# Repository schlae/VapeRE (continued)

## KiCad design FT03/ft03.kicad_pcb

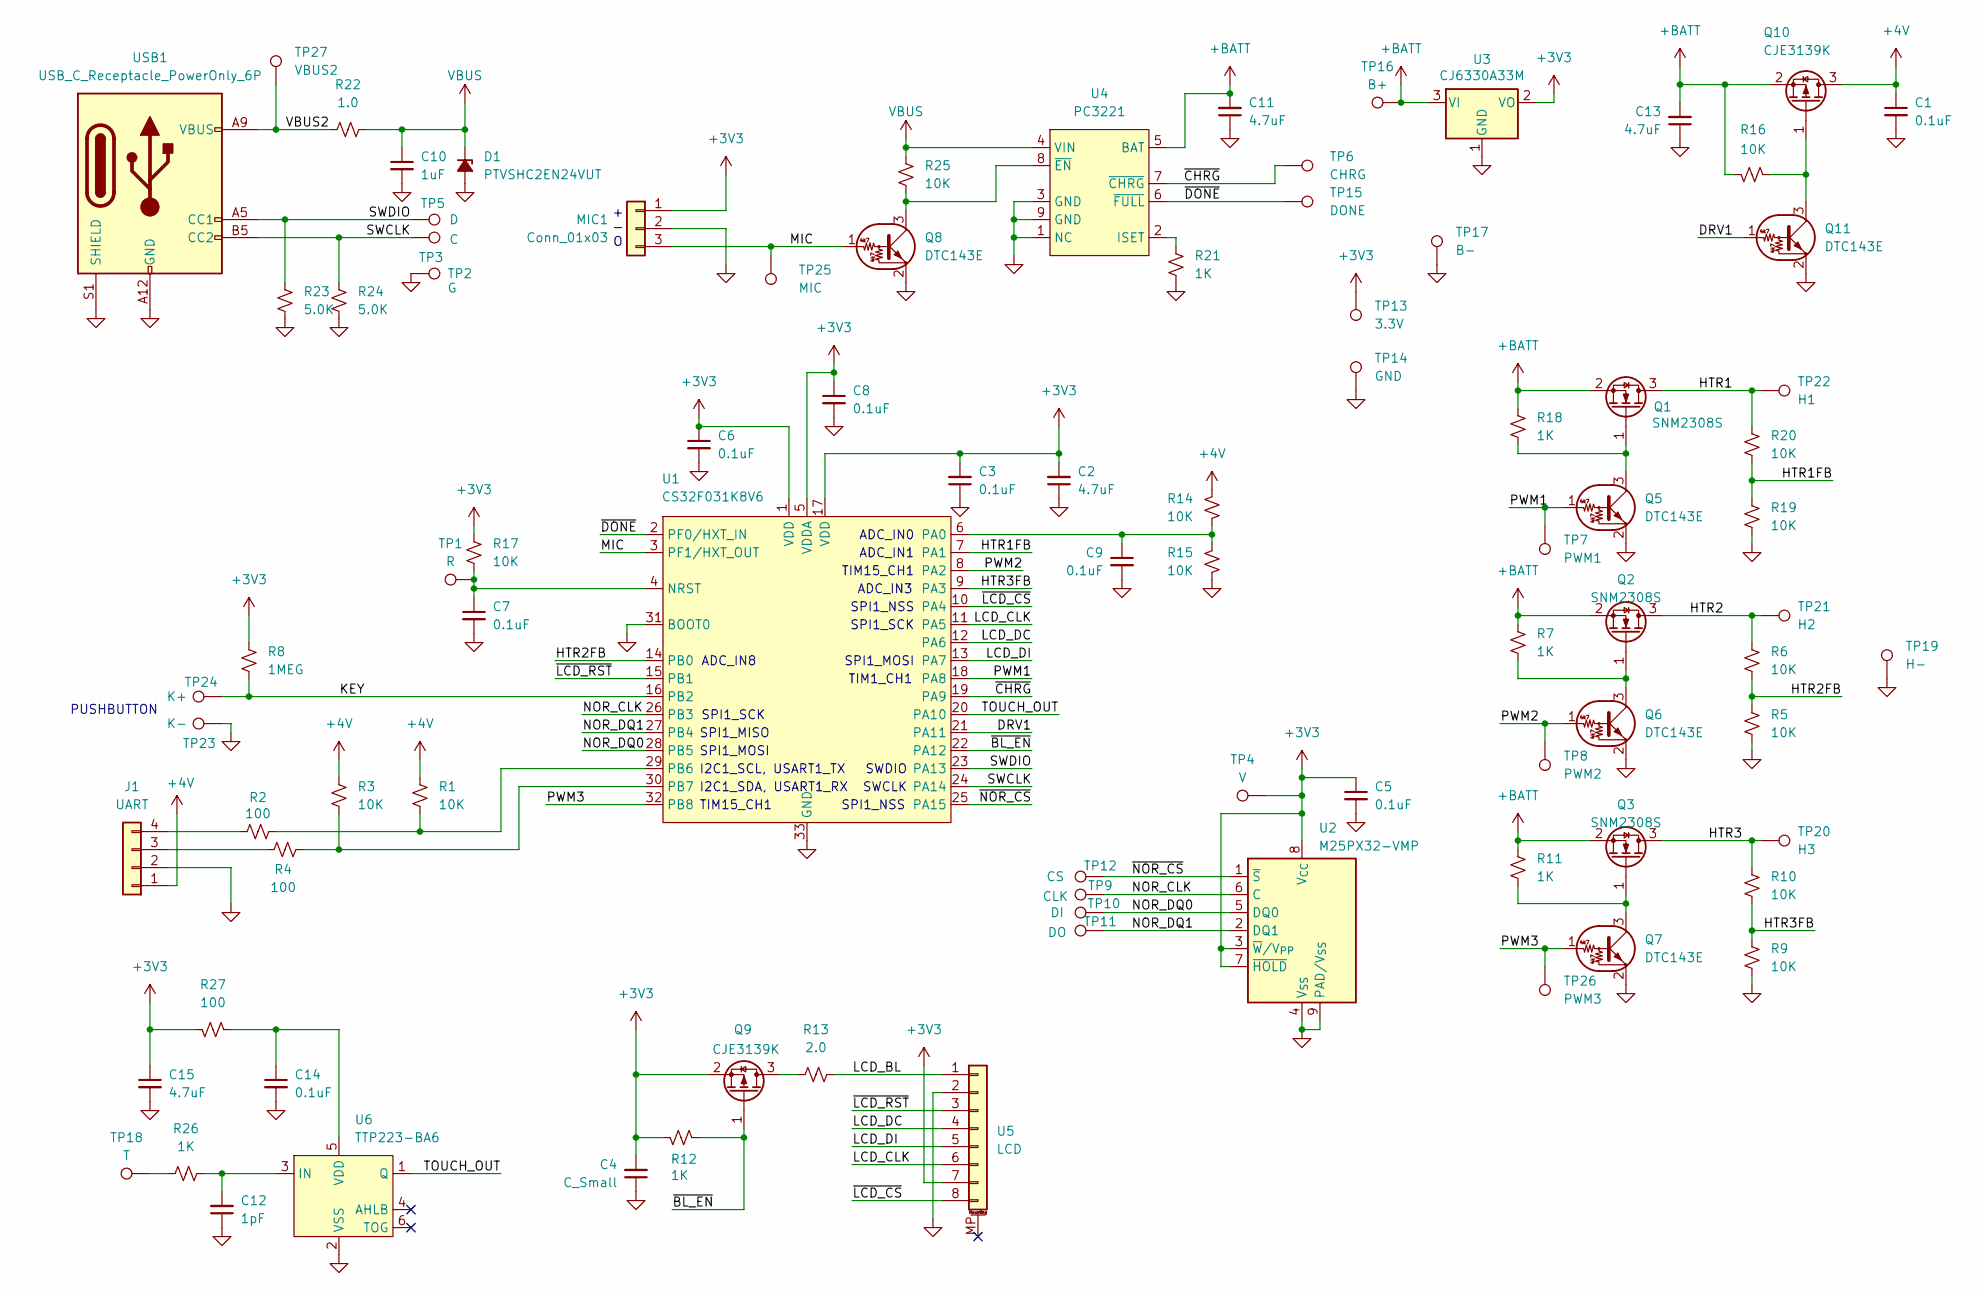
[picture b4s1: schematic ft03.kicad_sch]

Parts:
C1, C3, C5, C6, C7, C8, C9, C14: 0.1uF; C_0402_1005Metric
C2, C11, C13, C15: 4.7uF; C_0402_1005Metric
C4: C_Small; C_0402_1005Metric
C10: 1uF; C_0402_1005Metric
C12: 1pF; C_0402_1005Metric
D1: PTVSHC2EN24VUT; ST_QFN-2L_1.6x1.0mm
J1: UART; PinHeader_1x04_P2.00mm_Vertical
MIC1: Conn_01x03; MIC_3P
Q1, Q2, Q3: SNM2308S; SOT95P230X117-3
Q5, Q6, Q7, Q8, Q11: DTC143E; SOT-523
Q9, Q10: CJE3139K; SOT-523
R1, R3, R5, R6, R9, R10, R14, R15, R16, R17, R19, R20, R25: 10K; R_0402_1005Metric
R2, R4, R27: 100; R_0402_1005Metric
R7, R11, R12, R18, R21, R26: 1K; R_0402_1005Metric
R8: 1MEG; R_0402_1005Metric
R13: 2.0; R_0805_2012Metric
R22: 1.0; R_0805_2012Metric
R23, R24: 5.0K; R_0402_1005Metric
TP1: R; TestPoint_Pad_D1.0mm
TP2: G; TestPoint_Pad_D1.0mm
TP3: C; TestPoint_Pad_D1.0mm
TP4: V; TestPoint_Pad_D1.0mm
TP5: D; TestPoint_Pad_D1.0mm
TP6: CHRG; TestPoint_Pad_D1.0mm
TP7: PWM1; TestPoint_Pad_D1.0mm
TP8: PWM2; TestPoint_Pad_D1.0mm
TP9: CLK; TestPoint_Pad_D1.0mm
TP10: DI; TestPoint_Pad_D1.0mm
TP11: DO; TestPoint_Pad_D1.0mm
TP12: CS; TestPoint_Pad_D1.0mm
TP13: 3.3V; TestPoint_Pad_D1.0mm
TP14: GND; TestPoint_Pad_D1.0mm
TP15: DONE; TestPoint_Pad_D1.0mm
TP16: B+; TestPoint_Pad_D1.5mm
TP17: B-; TestPoint_Pad_D1.5mm
TP18: T; TestPoint_Pad_D1.5mm
TP19: H-; TestPoint_Pad_D1.5mm
TP20: H3; TestPoint_Pad_D1.5mm
TP21: H2; TestPoint_Pad_D1.5mm
TP22: H1; TestPoint_Pad_D1.5mm
TP23: K-; TestPoint_Pad_D1.5mm
TP24: K+; TestPoint_Pad_D1.5mm
TP25: MIC; TestPoint_Pad_D1.0mm
TP26: PWM3; TestPoint_Pad_D1.0mm
TP27: VBUS2; TestPoint_Pad_D1.5mm
U1: CS32F031K8V6; QFN-32-1EP_4x4mm_P0.4mm_EP2.9x2.9mm
U2: M25PX32-VMP; Winbond_USON-8-1EP_3x2mm_P0.5mm_EP0.2x1.6mm
U3: CJ6330A33M; SOT95P230X117-3
U4: PC3221; HSOP-8-1EP_3.9x4.9mm_P1.27mm_EP2.41x3.1mm
U5: LCD; UNK_FPC_1x08-1MP_P0.5mm_Horizontal
U6: TTP223-BA6; SOT95P305X110-6
USB1: USB_C_Receptacle_PowerOnly_6P; USB_C_Receptacle_HRO_TYPE-C-31-M-17

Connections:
+3V3: C2.2, C3.2, C4.2, C5.1, C6.1, C8.1, C15.1, MIC1.1, Q9.2 (S), R8.2, R12.1, R17.1, R27.2, TP4.1, TP13.1, U1.1 (VDD), U1.5 (VDDA), U1.17 (VDD), U2.3 (~W/V_{PP}), U2.7 (~HOLD), U2.8 (V_{CC}), U3.2 (VO), U5.7
+4V: C1.1, J1.1, Q10.3 (D), R1.1, R3.1, R14.2
+BATT: C11.2, C13.2, Q1.2 (S), Q2.2 (S), Q3.2 (S), Q10.2 (S), R7.1, R11.2, R16.2, R18.2, TP16.1, U3.3 (VI), U4.5 (BAT)
/DRV1: Q11.1 (B), U1.21 (PA11)
/HTR1: Q1.3 (D), R20.1, TP22.1
/HTR1FB: R19.1, R20.2, U1.7 (PA1)
/HTR2: Q2.3 (D), R6.1, TP21.1
/HTR2FB: R5.2, R6.2, U1.14 (PB0)
/HTR3: Q3.3 (D), R10.2, TP20.1
/HTR3FB: R9.1, R10.1, U1.9 (PA3)
/KEY: R8.1, TP24.1, U1.16 (PB2)
/LCD_BL: R13.2, U5.1
/LCD_CLK: U1.11 (PA5), U5.6
/LCD_DC: U1.12 (PA6), U5.4
/LCD_DI: U1.13 (PA7), U5.5
/MIC: MIC1.3, Q8.1 (B), TP25.1, U1.3 (PF1/HXT_OUT)
/NOR_CLK: TP9.1, U1.26 (PB3), U2.6 (C)
/NOR_DQ0: TP10.1, U1.28 (PB5), U2.5 (DQ0)
/NOR_DQ1: TP11.1, U1.27 (PB4), U2.2 (DQ1)
/PWM1: Q5.1 (B), TP7.1, U1.18 (PA8)
/PWM2: Q6.1 (B), TP8.1, U1.8 (PA2)
/PWM3: Q7.1 (B), TP26.1, U1.32 (PB8)
/SWCLK: R24.1, TP3.1, U1.24 (PA14), USB1.B5 (CC2)
/SWDIO: R23.1, TP5.1, U1.23 (PA13), USB1.A5 (CC1)
/TOUCH_OUT: U1.20 (PA10), U6.1 (Q)
/VBUS2: R22.2, TP27.1, USB1.A9 (VBUS), USB1.B9 (VBUS)
/~BL_EN: Q9.1 (G), R12.2, U1.22 (PA12)
/~CHRG: TP6.1, U1.19 (PA9), U4.7 (~CHRG)
/~DONE: TP15.1, U1.2 (PF0/HXT_IN), U4.6 (~FULL)
/~LCD_CS: U1.10 (PA4), U5.8
/~LCD_RST: U1.15 (PB1), U5.3
/~NOR_CS: TP12.1, U1.25 (PA15), U2.1 (~S)
GND: C1.2, C2.1, C3.1, C4.1, C5.2, C6.2, C7.2, C8.2, C9.2, C10.2, C11.1, C12.1, C13.1, C14.2, C15.2, D1.2 (A), J1.2, MIC1.2, Q5.2 (E), Q6.2 (E), Q7.2 (E), Q8.2 (E), Q11.2 (E), R5.1, R9.2, R15.1, R19.2, R21.2, R23.2, R24.2, TP2.1, TP14.1, TP17.1, TP19.1, TP23.1, U1.31 (BOOT0), U1.33 (GND), U2.4 (V_{SS}), U2.9 (PAD/V_{SS}), U3.1 (GND), U4.1 (NC), U4.3 (GND), U4.9 (GND), U5.2, U6.2 (VSS), USB1.A12 (GND), USB1.B12 (GND), USB1.S1 (SHIELD)
unnamed: J1.3, R4.1
unnamed: J1.4, R2.1
unnamed: Q1.1 (G), Q5.3 (C), R18.1
unnamed: Q2.1 (G), Q6.3 (C), R7.2
unnamed: Q3.1 (G), Q7.3 (C), R11.1
unnamed: Q8.3 (C), R25.1, U4.8 (~EN)
unnamed: Q9.3 (D), R13.1
unnamed: Q10.1 (G), Q11.3 (C), R16.1
unnamed: R26.1, TP18.1
unnamed: C7.1, R17.2, TP1.1, U1.4 (NRST)
unnamed: C9.1, R14.1, R15.2, U1.6 (PA0)
unnamed: R1.2, R2.2, U1.29 (PB6)
unnamed: R3.2, R4.2, U1.30 (PB7)
unnamed: R21.1, U4.2 (ISET)
unnamed: C12.2, R26.2, U6.3 (IN)
unnamed: C14.1, R27.1, U6.5 (VDD)
VBUS: C10.1, D1.1 (K), R22.1, R25.2, U4.4 (VIN)

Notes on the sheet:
SPI1_NSS
I2C1_SCL, USART1_TX
SPI1_SCK
SWDIO
ADC_IN1
SPI1_MOSI
I2C1_SDA, USART1_RX
SPI1_MISO
TIM1_CH1
TIM15_CH1
PUSHBUTTON
SWCLK
ADC_IN0
ADC_IN8
ADC_IN3
+ - O

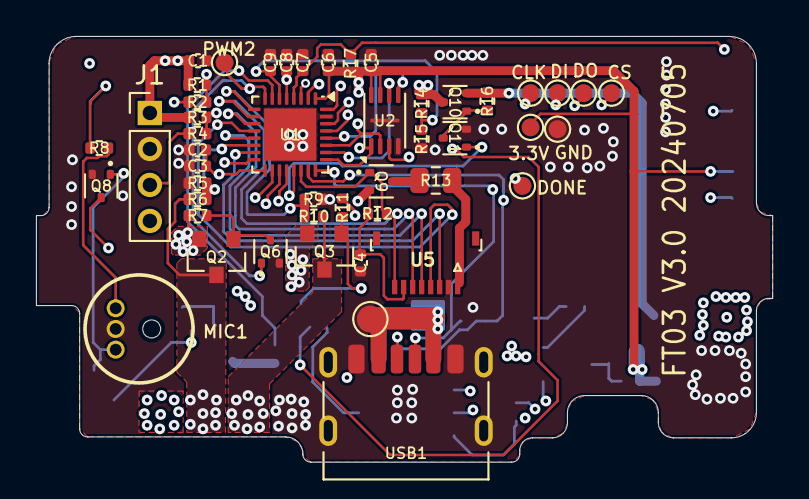
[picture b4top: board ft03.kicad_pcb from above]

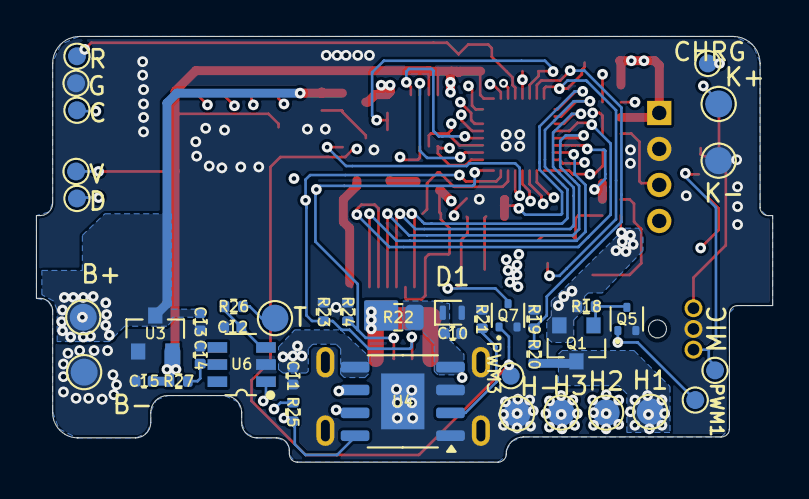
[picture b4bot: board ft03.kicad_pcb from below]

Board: 4 copper layers, 40.9 x 23.7 mm, 89 parts (41 on the bottom side), 50 nets.

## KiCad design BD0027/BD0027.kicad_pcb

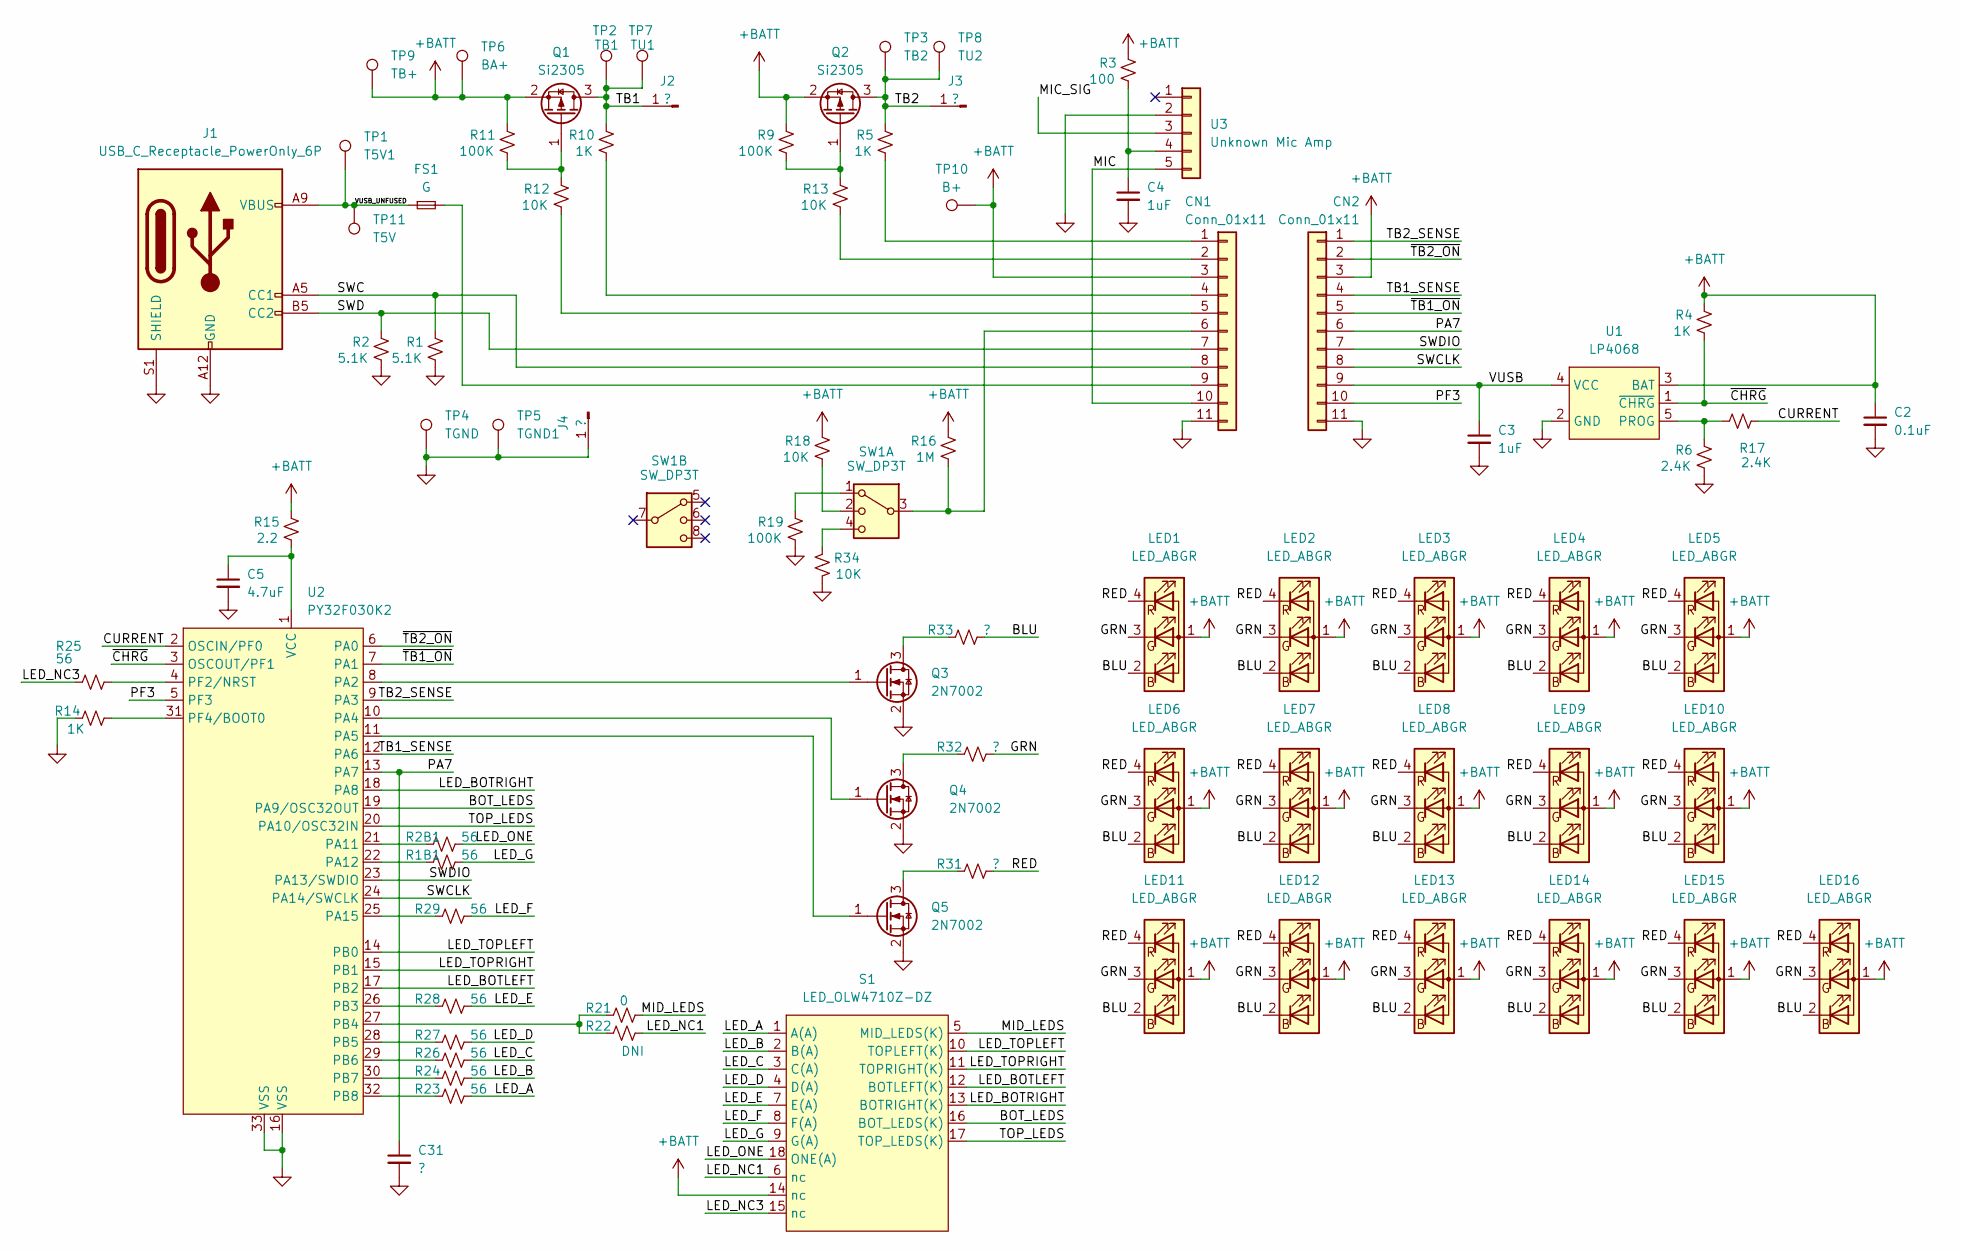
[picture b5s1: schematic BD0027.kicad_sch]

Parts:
C2: 0.1uF; C_0402_1005Metric
C3, C4: 1uF; C_0402_1005Metric
C5: 4.7uF; C_0402_1005Metric
C31: ?; C_0402_1005Metric
CN1, CN2: Conn_01x11; PinHeader_1x11_P1.00mm_Vertical
FS1: G; Fuse_0603_1608Metric
J1: USB_C_Receptacle_PowerOnly_6P; USB_C_Receptacle_TYPE-C-VERT
J2, J3, J4: ?; Pin_D1.2mm_L10.2mm_W2.9mm_FlatFork
LED1, LED2, LED3, LED4, LED5, LED6, LED7, LED8, LED9, LED10, LED11, LED12, LED13, LED14, LED15, LED16: LED_ABGR; LED_SK6812_EC15_1.5x1.5mm
Q1, Q2: Si2305; SOT95P230X117-3
Q3, Q4, Q5: 2N7002; SOT-523
R1, R2: 5.1K; R_0402_1005Metric
R1B1, R2B1, R23, R24, R25, R26, R27, R28, R29: 56; R_0402_1005Metric
R3: 100; R_0402_1005Metric
R4, R5, R10, R14: 1K; R_0402_1005Metric
R6, R17: 2.4K; R_0402_1005Metric
R9, R11, R19: 100K; R_0402_1005Metric
R12, R13, R18, R34: 10K; R_0402_1005Metric
R15: 2.2; R_0402_1005Metric
R16: 1M; R_0402_1005Metric
R21: 0; R_0402_1005Metric
R22: DNI; R_0402_1005Metric
R31, R32, R33: ?; R_0805_2012Metric
S1: LED_OLW4710Z-DZ; OLW4710Z-DZ
SW1: SW_DP3T; SW_DP3T_SMD
TP1: T5V1; TestPoint_Pad_D1.5mm
TP2: TB1; TestPoint_Pad_D1.5mm
TP3: TB2; TestPoint_Pad_D1.5mm
TP4: TGND; TestPoint_Pad_D1.5mm
TP5: TGND1; TestPoint_Pad_D1.5mm
TP6: BA+; TestPoint_Pad_D1.5mm
TP7: TU1; TestPoint_Pad_D1.5mm
TP8: TU2; TestPoint_Pad_D1.5mm
TP9: TB+; TestPoint_Pad_D1.5mm
TP10: B+; TestPoint_Pad_D1.5mm
TP11: T5V; TestPoint_Pad_D1.5mm
U1: LP4068; TSOP-5_1.65x3.05mm_P0.95mm
U2: PY32F030K2; QFN-32-1EP_5x5mm_P0.5mm_EP3.45x3.45mm
U3: Unknown Mic Amp; SOT-23-5

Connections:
+BATT: C2.1, CN1.3, CN2.3, LED1.1 (A), LED2.1 (A), LED3.1 (A), LED4.1 (A), LED5.1 (A), LED6.1 (A), LED7.1 (A), LED8.1 (A), LED9.1 (A), LED10.1 (A), LED11.1 (A), LED12.1 (A), LED13.1 (A), LED14.1 (A), LED15.1 (A), LED16.1 (A), Q1.2 (S), Q2.2 (S), R3.2, R4.2, R9.2, R11.2, R15.2, R16.2, R18.2, S1.14 (nc), TP6.1, TP9.1, TP10.1, U1.3 (BAT)
/BLU: LED1.2 (BK), LED2.2 (BK), LED3.2 (BK), LED4.2 (BK), LED5.2 (BK), LED6.2 (BK), LED7.2 (BK), LED8.2 (BK), LED9.2 (BK), LED10.2 (BK), LED11.2 (BK), LED12.2 (BK), LED13.2 (BK), LED14.2 (BK), LED15.2 (BK), LED16.2 (BK), R33.1
/BOT_LEDS: S1.16 (BOT_LEDS(K)), U2.19 (PA9/OSC32OUT)
/CURRENT: R17.1, U2.2 (OSCIN/PF0)
/GRN: LED1.3 (GK), LED2.3 (GK), LED3.3 (GK), LED4.3 (GK), LED5.3 (GK), LED6.3 (GK), LED7.3 (GK), LED8.3 (GK), LED9.3 (GK), LED10.3 (GK), LED11.3 (GK), LED12.3 (GK), LED13.3 (GK), LED14.3 (GK), LED15.3 (GK), LED16.3 (GK), R32.1
/LED_A: R23.1, S1.1 (A(A))
/LED_B: R24.1, S1.2 (B(A))
/LED_BOTLEFT: S1.12 (BOTLEFT(K)), U2.17 (PB2)
/LED_BOTRIGHT: S1.13 (BOTRIGHT(K)), U2.18 (PA8)
/LED_C: R26.1, S1.3 (C(A))
/LED_D: R27.1, S1.4 (D(A))
/LED_E: R28.1, S1.7 (E(A))
/LED_F: R29.1, S1.8 (F(A))
/LED_G: R1B1.1, S1.9 (G(A))
/LED_NC1: R22.1, S1.6 (nc)
/LED_NC3: R25.1, S1.15 (nc)
/LED_ONE: R2B1.1, S1.18 (ONE(A))
/LED_TOPLEFT: S1.10 (TOPLEFT(K)), U2.14 (PB0)
/LED_TOPRIGHT: S1.11 (TOPRIGHT(K)), U2.15 (PB1)
/MIC: CN1.10, U3.5
/MIC_SIG: U3.3
/MID_LEDS: R21.1, S1.5 (MID_LEDS(K))
/PA7: C31.1, CN2.6, U2.13 (PA7)
/PF3: CN2.10, U2.5 (PF3)
/RED: LED1.4 (RK), LED2.4 (RK), LED3.4 (RK), LED4.4 (RK), LED5.4 (RK), LED6.4 (RK), LED7.4 (RK), LED8.4 (RK), LED9.4 (RK), LED10.4 (RK), LED11.4 (RK), LED12.4 (RK), LED13.4 (RK), LED14.4 (RK), LED15.4 (RK), LED16.4 (RK), R31.1
/SWC: CN1.8, J1.A5 (CC1), R1.2
/SWCLK: CN2.8, U2.24 (PA14/SWCLK)
/SWD: CN1.7, J1.B5 (CC2), R2.2
/SWDIO: CN2.7, U2.23 (PA13/SWDIO)
/TB1: J2.1, Q1.3 (D), R10.2, TP2.1, TP7.1
/TB1_SENSE: CN2.4, U2.12 (PA6)
/TB2: J3.1, Q2.3 (D), R5.2, TP3.1, TP8.1
/TB2_SENSE: CN2.1, U2.9 (PA3)
/TOP_LEDS: S1.17 (TOP_LEDS(K)), U2.20 (PA10/OSC32IN)
/VUSB: C3.1, CN2.9, U1.4 (VCC)
/VUSB_UNFUSED: FS1.1, J1.A9 (VBUS), J1.B9 (VBUS), TP1.1, TP11.1
/~CHRG: R4.1, U1.1 (~CHRG), U2.3 (OSCOUT/PF1)
/~TB1_ON: CN2.5, U2.7 (PA1)
/~TB2_ON: CN2.2, U2.6 (PA0)
GND: C2.2, C3.2, C4.2, C5.2, C31.2, CN1.11, CN2.11, J1.A12 (GND), J1.B12 (GND), J1.S1 (SHIELD), J4.1, Q3.2 (S), Q4.2 (S), Q5.2 (S), R1.1, R2.1, R6.1, R14.2, R19.1, R34.1, TP4.1, TP5.1, U1.2 (GND), U2.16 (VSS), U2.33 (VSS), U3.2
unnamed: CN1.1, R5.1
unnamed: CN1.2, R13.1
unnamed: CN1.4, R10.1
unnamed: CN1.5, R12.1
unnamed: CN1.6, R16.1, SW1.3
unnamed: CN1.9, FS1.2
unnamed: Q1.1 (G), R11.1, R12.2
unnamed: Q2.1 (G), R9.1, R13.2
unnamed: Q3.3 (D), R33.2
unnamed: Q3.1 (G), U2.8 (PA2)
unnamed: Q4.3 (D), R32.2
unnamed: Q4.1 (G), U2.10 (PA4)
unnamed: Q5.3 (D), R31.2
unnamed: Q5.1 (G), U2.11 (PA5)
unnamed: R18.1, SW1.2
unnamed: R19.2, SW1.1
unnamed: R34.2, SW1.4
unnamed: R6.2, R17.2, U1.5 (PROG)
unnamed: R2B1.2, U2.21 (PA11)
unnamed: R1B1.2, U2.22 (PA12)
unnamed: R29.2, U2.25 (PA15)
unnamed: R28.2, U2.26 (PB3)
unnamed: R21.2, R22.2, U2.27 (PB4)
unnamed: R27.2, U2.28 (PB5)
unnamed: R26.2, U2.29 (PB6)
unnamed: R24.2, U2.30 (PB7)
unnamed: R23.2, U2.32 (PB8)
unnamed: R25.2, U2.4 (PF2/NRST)
unnamed: R14.1, U2.31 (PF4/BOOT0)
unnamed: C5.1, R15.1, U2.1 (VCC)
unnamed: C4.1, R3.1, U3.4

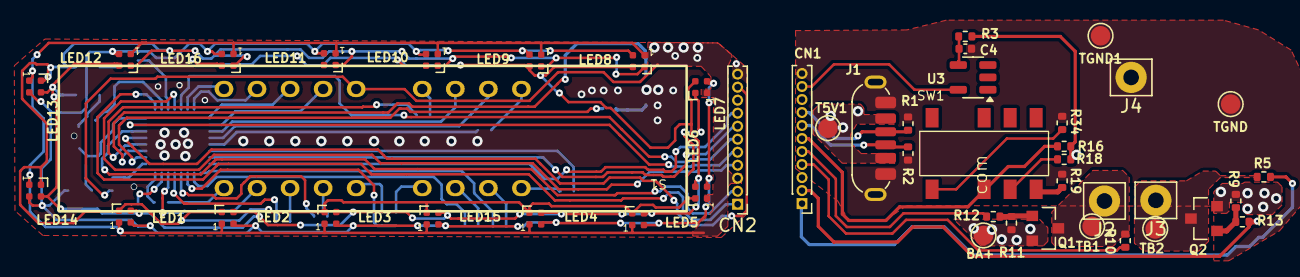
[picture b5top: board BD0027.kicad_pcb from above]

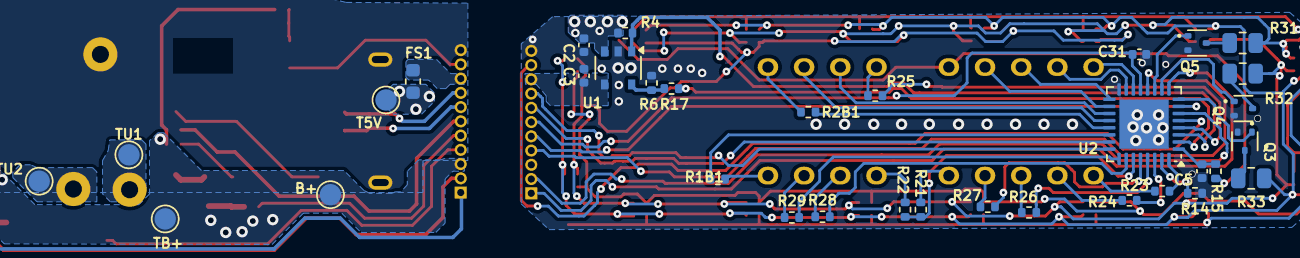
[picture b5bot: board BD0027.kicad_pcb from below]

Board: 2 copper layers, 81 parts (34 on the bottom side), 70 nets.

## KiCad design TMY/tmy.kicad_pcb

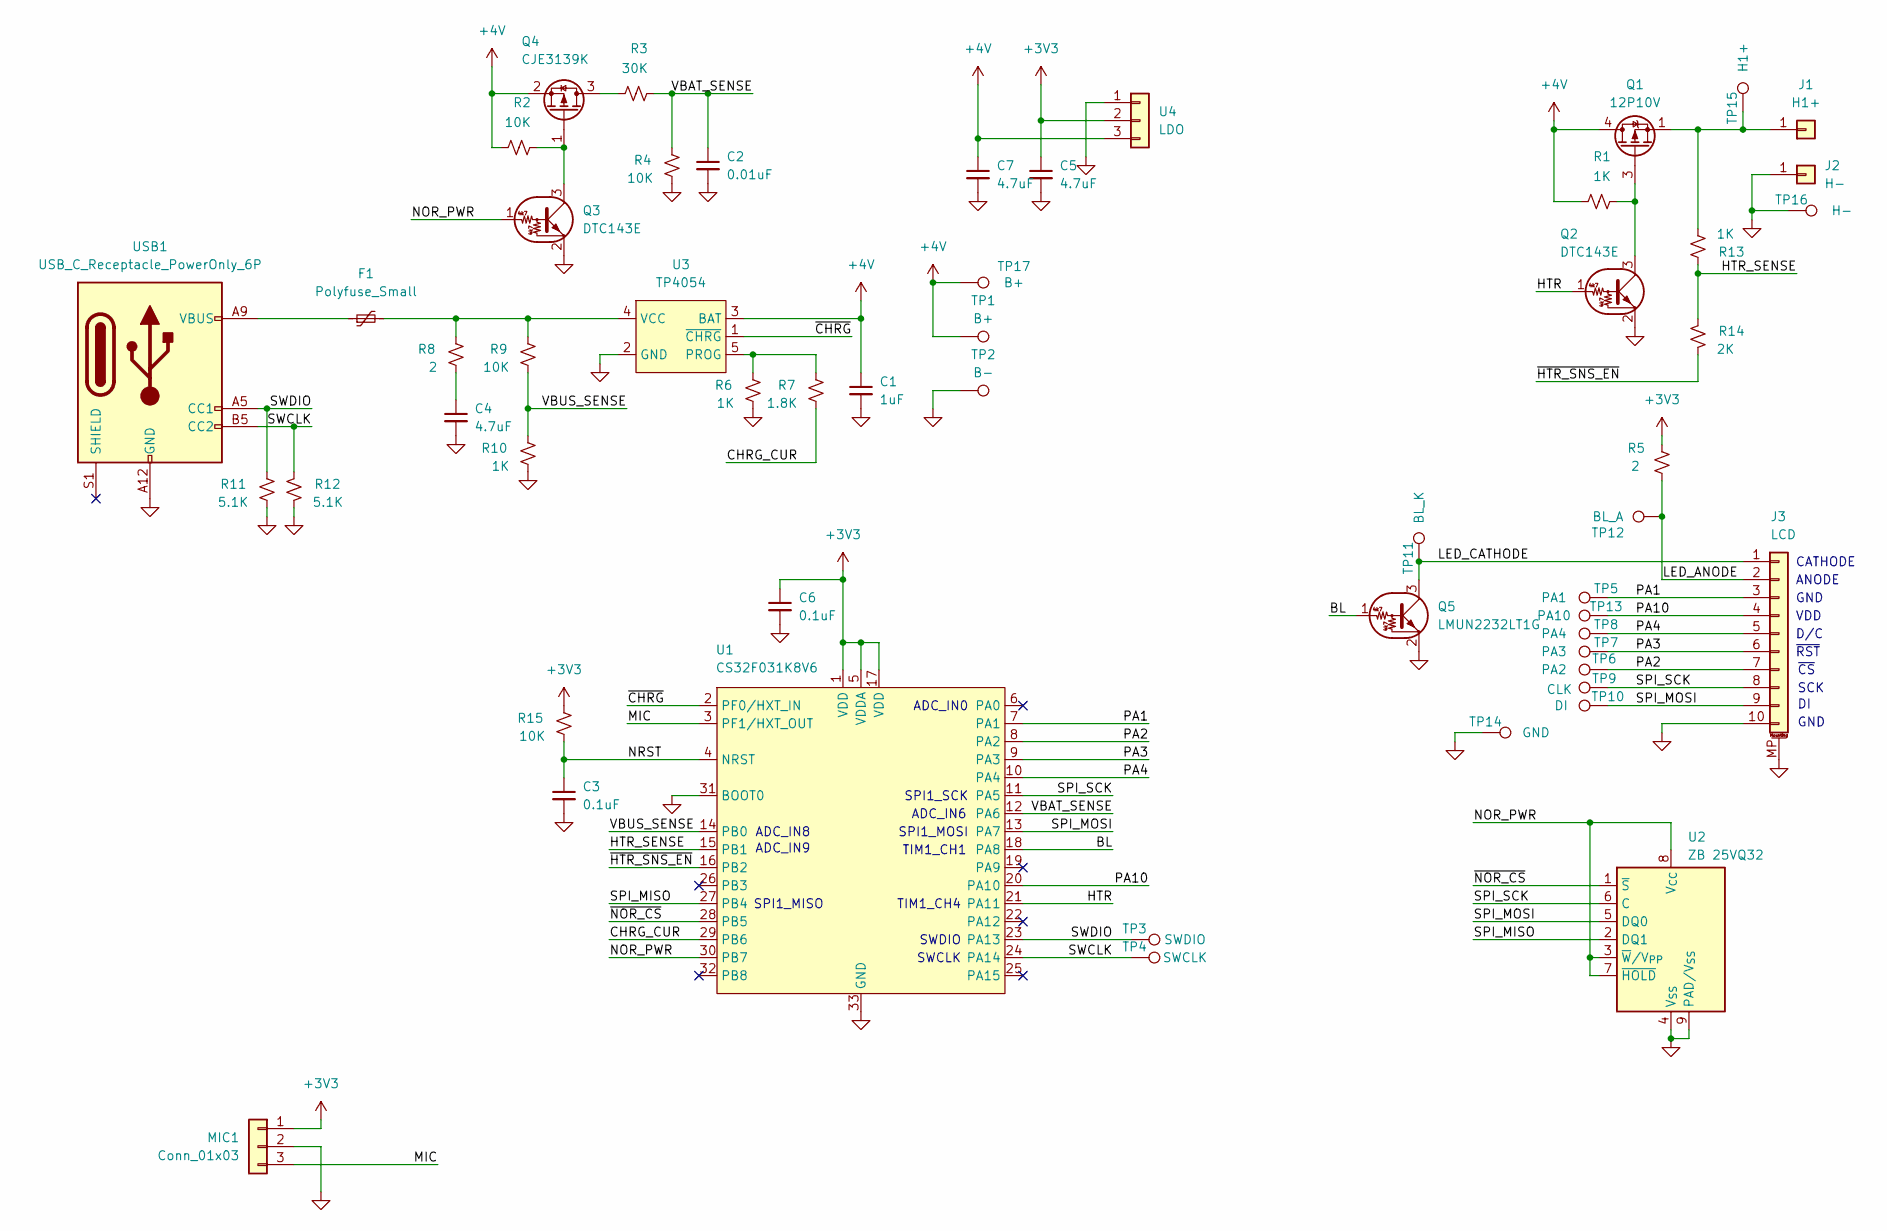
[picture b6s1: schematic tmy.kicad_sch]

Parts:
C1: 1uF; C_0402_1005Metric
C2: 0.01uF; C_0402_1005Metric
C3, C6: 0.1uF; C_0402_1005Metric
C4, C5, C7: 4.7uF; C_0402_1005Metric
F1: Polyfuse_Small; Fuse_0603_1608Metric
J1: H1+; TestPoint_THTPad_D1.5mm_Drill0.7mm
J2: H-; TestPoint_THTPad_D1.5mm_Drill0.7mm
J3: LCD; UNK_FPC_1x10-1MP_P0.5mm_Horizontal
MIC1: Conn_01x03; MIC_3P_Alt
Q1: 12P10V; Texas_DQK
Q2, Q3: DTC143E; SOT-523
Q4: CJE3139K; SOT-523
Q5: LMUN2232LT1G; SC-59
R1, R6, R10, R13: 1K; R_0402_1005Metric
R2, R4, R9, R15: 10K; R_0402_1005Metric
R3: 30K; R_0402_1005Metric
R5: 2; R_0603_1608Metric
R7: 1.8K; R_0402_1005Metric
R8: 2; R_0402_1005Metric
R11, R12: 5.1K; R_0402_1005Metric
R14: 2K; R_0402_1005Metric
TP1, TP17: B+; TestPoint_Pad_D1.5mm
TP2: B-; TestPoint_Pad_D1.5mm
TP3: SWDIO; TestPoint_Pad_D1.0mm
TP4: SWCLK; TestPoint_Pad_D1.0mm
TP5: PA1; TestPoint_Pad_D1.0mm
TP6: PA2; TestPoint_Pad_D1.0mm
TP7: PA3; TestPoint_Pad_D1.0mm
TP8: PA4; TestPoint_Pad_D1.0mm
TP9: CLK; TestPoint_Pad_D1.0mm
TP10: DI; TestPoint_Pad_D1.0mm
TP11: BL_K; TestPoint_Pad_D1.0mm
TP12: BL_A; TestPoint_Pad_D1.0mm
TP13: PA10; TestPoint_Pad_D1.0mm
TP14: GND; TestPoint_Pad_D1.0mm
TP15: H1+; TestPoint_Pad_D1.0mm
TP16: H-; TestPoint_Pad_D1.0mm
U1: CS32F031K8V6; QFN-32-1EP_4x4mm_P0.4mm_EP2.9x2.9mm
U2: ZB 25VQ32; Winbond_USON-8-1EP_3x2mm_P0.5mm_EP0.2x1.6mm
U3: TP4054; TSOP-5_1.65x3.05mm_P0.95mm
U4: LDO; SOT95P230X117-3
USB1: USB_C_Receptacle_PowerOnly_6P; USB_C_Receptacle_TYPE-C-VERT

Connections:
+3V3: C5.1, C6.1, MIC1.1, R5.2, R15.2, U1.1 (VDD), U1.5 (VDDA), U1.17 (VDD), U4.2
+4V: C1.1, C7.1, Q1.4 (D), Q1.7 (D), Q4.2 (S), R1.1, R2.1, TP1.1, TP17.1, U3.3 (BAT), U4.3
/BL: Q5.1 (B), U1.18 (PA8)
/CHRG_CUR: R7.1, U1.29 (PB6)
/HTR: Q2.1 (B), U1.21 (PA11)
/HTR_SENSE: R13.2, R14.2, U1.15 (PB1)
/LED_ANODE: J3.2, R5.1, TP12.1
/LED_CATHODE: J3.1, Q5.3 (C), TP11.1
/MIC: MIC1.3, U1.3 (PF1/HXT_OUT)
/NOR_PWR: Q3.1 (B), U1.30 (PB7), U2.3 (~W/V_{PP}), U2.7 (~HOLD), U2.8 (V_{CC})
/NRST: C3.1, R15.1, U1.4 (NRST)
/PA1: J3.3, TP5.1, U1.7 (PA1)
/PA2: J3.7, TP6.1, U1.8 (PA2)
/PA3: J3.6, TP7.1, U1.9 (PA3)
/PA4: J3.5, TP8.1, U1.10 (PA4)
/PA10: J3.4, TP13.1, U1.20 (PA10)
/SPI_MISO: U1.27 (PB4), U2.2 (DQ1)
/SPI_MOSI: J3.9, TP10.1, U1.13 (PA7), U2.5 (DQ0)
/SPI_SCK: J3.8, TP9.1, U1.11 (PA5), U2.6 (C)
/SWCLK: R12.2, TP4.1, U1.24 (PA14), USB1.B5 (CC2)
/SWDIO: R11.2, TP3.1, U1.23 (PA13), USB1.A5 (CC1)
/VBAT_SENSE: C2.1, R3.2, R4.2, U1.12 (PA6)
/VBUS_SENSE: R9.1, R10.2, U1.14 (PB0)
/~CHRG: U1.2 (PF0/HXT_IN), U3.1 (~CHRG)
/~HTR_SNS_EN: R14.1, U1.16 (PB2)
/~NOR_CS: U1.28 (PB5), U2.1 (~S)
GND: C1.2, C2.2, C3.2, C4.2, C5.2, C6.2, C7.2, J2.1, J3.10, J3.MP (MountPin), MIC1.2, Q2.2 (E), Q3.2 (E), Q5.2 (E), R4.1, R6.1, R10.1, R11.1, R12.1, TP2.1, TP14.1, TP16.1, U1.31 (BOOT0), U1.33 (GND), U2.4 (V_{SS}), U2.9 (PAD/V_{SS}), U3.2 (GND), U4.1, USB1.A12 (GND), USB1.B12 (GND)
unnamed: C4.1, R8.1
unnamed: F1.1, USB1.A9 (VBUS), USB1.B9 (VBUS)
unnamed: J1.1, Q1.1 (S), Q1.2 (S), Q1.5 (S), Q1.6 (S), Q1.8 (S), R13.1, TP15.1
unnamed: Q1.3 (G), Q2.3 (C), R1.2
unnamed: Q3.3 (C), Q4.1 (G), R2.2
unnamed: Q4.3 (D), R3.1
unnamed: R6.2, R7.2, U3.5 (PROG)
unnamed: F1.2, R8.2, R9.2, U3.4 (VCC)

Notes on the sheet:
SPI1_SCK
~{CS}
~{RST}
TIM1_CH4
ADC_IN6
SCK
SWCLK
ADC_IN8
ADC_IN9
GND
TIM1_CH1
ADC_IN0
SWDIO
SPI1_MISO
ANODE
SPI1_MOSI
CATHODE
D/C
VDD

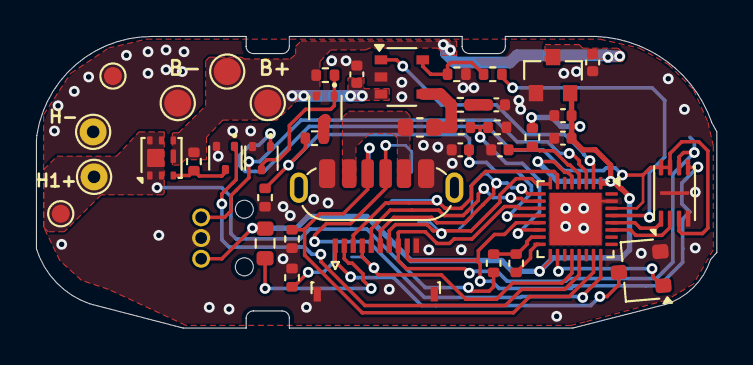
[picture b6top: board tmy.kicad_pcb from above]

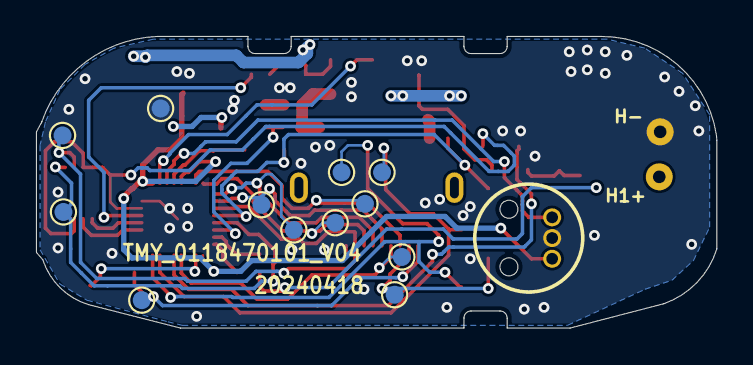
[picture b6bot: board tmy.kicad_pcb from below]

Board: 2 copper layers, 37.8 x 16.2 mm, 54 parts (13 on the bottom side), 35 nets.

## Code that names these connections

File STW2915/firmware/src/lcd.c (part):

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#include "nor.h"

#define LCD_PWR GPIO_PIN_8
#define LCD_DC GPIO_PIN_15
#define LCD_CS GPIO_PIN_7
#define LCD_RST GPIO_PIN_6
#define LCD_BACKLIGHT GPIO_PIN_8

#define CMD_NOP         0x00
#define CMD_PRIVATE     0xFD
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    HAL_GPIO_WritePin(GPIOA, LCD_PWR, GPIO_PIN_RESET);

    // Turn on LCD backlight
    HAL_GPIO_Init(GPIOB, &(GPIO_InitTypeDef){.Mode = GPIO_MODE_OUTPUT_PP, .Pin = LCD_BACKLIGHT});
    HAL_GPIO_WritePin(GPIOB, LCD_BACKLIGHT, GPIO_PIN_RESET);
    // Configure SPI for LCD
    // DI = PB5
    // CLK = PB3
    // RST = PB6
    // CS = PB7
    // C#/D = PA15
    HAL_GPIO_Init(GPIOB, &(GPIO_InitTypeDef){.Mode = GPIO_MODE_AF_PP, .Alternate = GPIO_AF0_SPI1, .Pin = GPIO_PIN_5});
    HAL_GPIO_Init(GPIOB, &(GPIO_InitTypeDef){.Mode = GPIO_MODE_AF_PP, .Alternate = GPIO_AF0_SPI1, .Pin = GPIO_PIN_3});

    HAL_GPIO_Init(GPIOB, &(GPIO_InitTypeDef){.Mode = GPIO_MODE_OUTPUT_PP, .Pin = LCD_RST});
    HAL_GPIO_WritePin(GPIOB, LCD_RST, GPIO_PIN_RESET);
    HAL_GPIO_Init(GPIOB, &(GPIO_InitTypeDef){.Mode = GPIO_MODE_OUTPUT_PP, .Pin = LCD_CS});
    HAL_GPIO_WritePin(GPIOB, LCD_CS, GPIO_PIN_RESET);
    HAL_GPIO_Init(GPIOA, &(GPIO_InitTypeDef){.Mode = GPIO_MODE_OUTPUT_PP, .Pin = LCD_DC});
    HAL_GPIO_WritePin(GPIOB, LCD_DC, GPIO_PIN_RESET);
}


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
static inline void mode_cmd()
{
    HAL_GPIO_WritePin(GPIOA, LCD_DC, GPIO_PIN_RESET);
}


static inline void mode_data()
{
    HAL_GPIO_WritePin(GPIOA, LCD_DC, GPIO_PIN_SET);
}


static inline void cs_low()
{
    HAL_GPIO_WritePin(GPIOB, LCD_CS, GPIO_PIN_RESET);
}


static inline void cs_high()
{
    HAL_GPIO_WritePin(GPIOB, LCD_CS, GPIO_PIN_SET);
}


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{
    _x_offset = 18;
    _y_offset = 82;
    HAL_GPIO_WritePin(GPIOB, LCD_CS, GPIO_PIN_SET);
    HAL_Delay(24);
    HAL_GPIO_WritePin(GPIOB, LCD_RST, GPIO_PIN_SET);
    HAL_Delay(6);
    HAL_GPIO_WritePin(GPIOB, LCD_RST, GPIO_PIN_RESET);
    HAL_Delay(50);
    HAL_GPIO_WritePin(GPIOB, LCD_RST, GPIO_PIN_SET);
    HAL_Delay(100); // Needed delay to allow LCD to init properly.

    // Configure registers
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    __HAL_RCC_DMA_CLK_DISABLE();
 
    // Turn off LCD backlight
    HAL_GPIO_WritePin(GPIOB, LCD_BACKLIGHT, GPIO_PIN_SET);

    // Float LCD controller pins
    HAL_GPIO_Init(GPIOB, &(GPIO_InitTypeDef){.Mode = GPIO_MODE_ANALOG, .Pin = GPIO_PIN_5});
    HAL_GPIO_Init(GPIOB, &(GPIO_InitTypeDef){.Mode = GPIO_MODE_ANALOG, .Pin = GPIO_PIN_3});
    HAL_GPIO_Init(GPIOB, &(GPIO_InitTypeDef){.Mode = GPIO_MODE_ANALOG, .Pin = LCD_RST});
    HAL_GPIO_Init(GPIOB, &(GPIO_InitTypeDef){.Mode = GPIO_MODE_ANALOG, .Pin = LCD_CS});
    HAL_GPIO_Init(GPIOA, &(GPIO_InitTypeDef){.Mode = GPIO_MODE_ANALOG, .Pin = LCD_DC});
}

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
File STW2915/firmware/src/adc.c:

// Copyright (C) 2025 Tube Time. See LICENSE file for license.

#include <stdio.h>
#include <stdbool.h>
#include <string.h>
#include "py32f0xx.h"

ADC_HandleTypeDef hadc;


void adc_init(void)
{
    __HAL_RCC_ADC_FORCE_RESET();
    __HAL_RCC_ADC_RELEASE_RESET();
    __HAL_RCC_ADC_CLK_ENABLE();

    // Turn on battery voltage monitoring resistor divider
    HAL_GPIO_Init(GPIOA, &(GPIO_InitTypeDef){.Mode = GPIO_MODE_OUTPUT_OD, .Pin = GPIO_PIN_12});
    HAL_GPIO_WritePin(GPIOA, GPIO_PIN_12, GPIO_PIN_RESET);

    // Turn on ADC channel
    HAL_GPIO_Init(GPIOA, &(GPIO_InitTypeDef){.Mode = GPIO_MODE_ANALOG, .Pin = GPIO_PIN_0}); // USB V
    HAL_GPIO_Init(GPIOB, &(GPIO_InitTypeDef){.Mode = GPIO_MODE_ANALOG, .Pin = GPIO_PIN_1}); // Batt V
    HAL_GPIO_Init(GPIOF, &(GPIO_InitTypeDef){.Mode = GPIO_MODE_ANALOG, .Pin = GPIO_PIN_2}); // Chg I

    hadc.Instance = ADC1;
    hadc.Init.ClockPrescaler = ADC_CLOCK_SYNC_PCLK_DIV8; // 6MHz. Also try ADC_CLOCK_ASYNC_HSI_DIV1
    hadc.Init.Resolution = ADC_RESOLUTION_12B;
    hadc.Init.DataAlign = ADC_DATAALIGN_RIGHT;
    hadc.Init.ScanConvMode = ADC_SCAN_DIRECTION_FORWARD;
    hadc.Init.ContinuousConvMode = DISABLE;
    hadc.Init.DiscontinuousConvMode = DISABLE;
    hadc.Init.ExternalTrigConvEdge = ADC_EXTERNALTRIGCONVEDGE_NONE;
    hadc.Init.ExternalTrigConv = ADC_SOFTWARE_START;
    hadc.Init.EOCSelection = ADC_EOC_SINGLE_CONV;
    hadc.Init.Overrun = ADC_OVR_DATA_OVERWRITTEN;
    hadc.Init.LowPowerAutoWait = ENABLE; // was disable
    hadc.Init.DMAContinuousRequests = DISABLE;
    // tADC = (3.5 + 13.5) * (1/12MHz) = 1.4167us > 1us min (ok)
    hadc.Init.SamplingTimeCommon = ADC_SAMPLETIME_239CYCLES_5; // Was 13CYCLES_5, trying longest for now.
    HAL_ADC_Init(&hadc);

    HAL_ADCEx_Calibration_Start(&hadc); // Run calibration before HAL_ADC_Start()
}


uint32_t get_adc(int channel)
{
    uint32_t adc_val;
    ADC_ChannelConfTypeDef sconfig = {0};

    // Select the channel
    sconfig.Channel = channel;
    sconfig.Rank = ADC_RANK_CHANNEL_NUMBER;
    sconfig.SamplingTime = ADC_SAMPLETIME_239CYCLES_5; 
    HAL_ADC_ConfigChannel(&hadc, &sconfig);

    // Do the conversion
    HAL_ADC_Start(&hadc);
    HAL_ADC_PollForConversion(&hadc, HAL_MAX_DELAY);
    adc_val = HAL_ADC_GetValue(&hadc);
    HAL_ADC_Stop(&hadc);

    // Disable the channel. This is required by all PY32 devices
    // but poorly documented and not done in any sample code.
    sconfig.Rank = ADC_RANK_NONE;
    HAL_ADC_ConfigChannel(&hadc, &sconfig);
   
    return adc_val;
}


void adc_sleep()
{
    // Shut off battery monitoring resistor divider enable
    HAL_GPIO_Init(GPIOA, &(GPIO_InitTypeDef){.Mode = GPIO_MODE_ANALOG, .Pin = GPIO_PIN_12}); // EN_MON_BAT

    HAL_GPIO_Init(GPIOA, &(GPIO_InitTypeDef){.Mode = GPIO_MODE_ANALOG, .Pin = GPIO_PIN_0}); // MON_USB
    HAL_GPIO_Init(GPIOA, &(GPIO_InitTypeDef){.Mode = GPIO_MODE_ANALOG, .Pin = GPIO_PIN_2}); // MON_F2
    HAL_GPIO_Init(GPIOA, &(GPIO_InitTypeDef){.Mode = GPIO_MODE_ANALOG, .Pin = GPIO_PIN_3}); // MON_F1
    HAL_GPIO_Init(GPIOF, &(GPIO_InitTypeDef){.Mode = GPIO_MODE_ANALOG, .Pin = GPIO_PIN_3}); // EN_MON_F1
    HAL_GPIO_Init(GPIOB, &(GPIO_InitTypeDef){.Mode = GPIO_MODE_ANALOG, .Pin = GPIO_PIN_4}); // EN_MON_F2
    HAL_GPIO_Init(GPIOA, &(GPIO_InitTypeDef){.Mode = GPIO_MODE_ANALOG, .Pin = GPIO_PIN_4}); // EN_F2
    HAL_GPIO_Init(GPIOF, &(GPIO_InitTypeDef){.Mode = GPIO_MODE_ANALOG, .Pin = GPIO_PIN_4}); // EN_F1

    HAL_ADC_DeInit(&hadc);
    __HAL_RCC_ADC_CLK_DISABLE();
}

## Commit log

2025-09-24 FT03
2025-09-24 TTP223
2025-09-26 Add LCD flex to layout
2025-09-26 Add TMY
2025-09-26 add LCD pinout
2025-10-07 Initial version of YK761
2025-10-07 Add values
2025-10-09 Complete YK761
2025-10-11 Add BD0027
2025-10-14 LDO regulator p/n
2025-10-14 Add STW2915
2025-10-17 Add BD0061
2025-11-01 STW2915 tweaks
2025-11-01 PY32 Firmware for STW2915
2025-11-01 Add license
2025-11-01 README
